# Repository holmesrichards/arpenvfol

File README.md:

# ARP Envelope follower

This is an envelope follower (EF) module in Kosmo format with mic and instrument preamplifiers.

It is a design based on the ARP 2600 — there’s a schematic in the [service manual](https://usermanual.wiki/Document/Arp2600ServiceManual.2176328765). Aside from changing the op amps to TL074 and reducing the output stage gain (which it seemed to need, maybe because it uses ±12 V instead of the ARP's ±15 V) the EF core is essentially identical to the original.

The ARP EF also has a preamplifier section for input of external, non-synth level signals which, of course, are what you’re going to use an EF on a lot of the time. Rather than try to adapt the Teledyne 1339 based design I replaced the ARP preamp with two different preamps: One to boost instrument levels to synth levels, and one to boost mic levels to instrument levels — which then goes through the other preamp as well. This is inspired by Eddie Bergman's [stripboard build](https://www.eddybergman.com/2020/02/synthesizer-build-part-20-arp2600.html), though I used different preamp circuits. The mic preamp is from a [design](http://www.zen22142.zen.co.uk/Circuits/Audio/ecmmic.htm) by Andy Collinson (with a mod from [here](https://electronics.stackexchange.com/questions/324047/%20what-is-the-best-preamplifier-circuit-for-electret-condenser-microphone)) while the instrument preamp is based on the one in Ken Stone’s [Stomp Box Adapter](https://sdiy.info/wiki/CGS_stomp_box_adapter_(smaller_version)). The mic preamp jack supplies power for a two terminal electret condenser mic. For a dynamic mic you may be able to use the instrument input, though I have not tested this.

If nothing’s plugged into the synth input it uses the output of the instrument preamp, and if nothing’s plugged into the input of the instrument preamp it uses the output of the mic preamp. And if nothing’s plugged into the input of the mic preamp it uses the condenser mic capsule mounted on the front panel! Yes, this module is always listening, so be careful what you say. Besides going to the EF input, the instrument preamp output goes to a front panel jack, so you can use this module to feed external signals (or the front panel mic) to other modules too.

This module isn't really a plug and play kind of thing. The output levels you get depend not only on the amplitude of the input signal but the waveform — square waves give bigger outputs than ramp waves, for instance. With an external signal source you will want to use the gain knob to get the preamp output up to around 10 Vpp, and then use the signal level knob to get the output to the right level. It's probably a good idea to use a scope to check your settings.

## Current draw
11.3 mA +12 V, 7.7 mA -12 V

## Photos

## Documentation

* [Schematic](Docs/arpenvfol.pdf)
* PCB layout: [front](Docs/_layout_front.pdf), [back](Docs/_layout_back.pdf)
* [BOM](Docs/arpenvfol_bom.md)
* [Build notes](Docs/build.md)
* [Blog post](https://analogoutputblog.wordpress.com/2022/05/04/arp-2600-based-envelope-follower/)

## GitHub repository

* [https://github.com/holmesrichards/arpenvfol](https://github.com/holmesrichards/arpenvfol)

## Submodules

This repo uses submodules aoKicad and Kosmo_panel, which provide needed libaries for KiCad. To clone:

```
git clone git@github.com:holmesrichards/arpenvfol.git
git submodule init
git submodule update
```

Alternatively do

```
git clone --recurse-submodules git@github.com:holmesrichards/arpenvfol.git
```

Or if you download the repository as a zip file, you must also click on the "aoKicad" and "Kosmo\_panel" links on the GitHub page (they'll have "@ something" after them) and download them as separate zip files which you can unzip into this repo's aoKicad and Kosmo\_panel directories.

If desired, copy the files from aoKicad and Kosmo\_panel to wherever you prefer (your KiCad user library directory, for instance, if you have one). Then in KiCad, go into Edit Symbols and add symbol libraries 

```
aoKicad/ao_symbols
Kosmo_panel/Kosmo
```
and go into Edit Footprints and add footprint libraries 
```
aoKicad/ao_tht
Kosmo_panel/Kosmo_panel.
```

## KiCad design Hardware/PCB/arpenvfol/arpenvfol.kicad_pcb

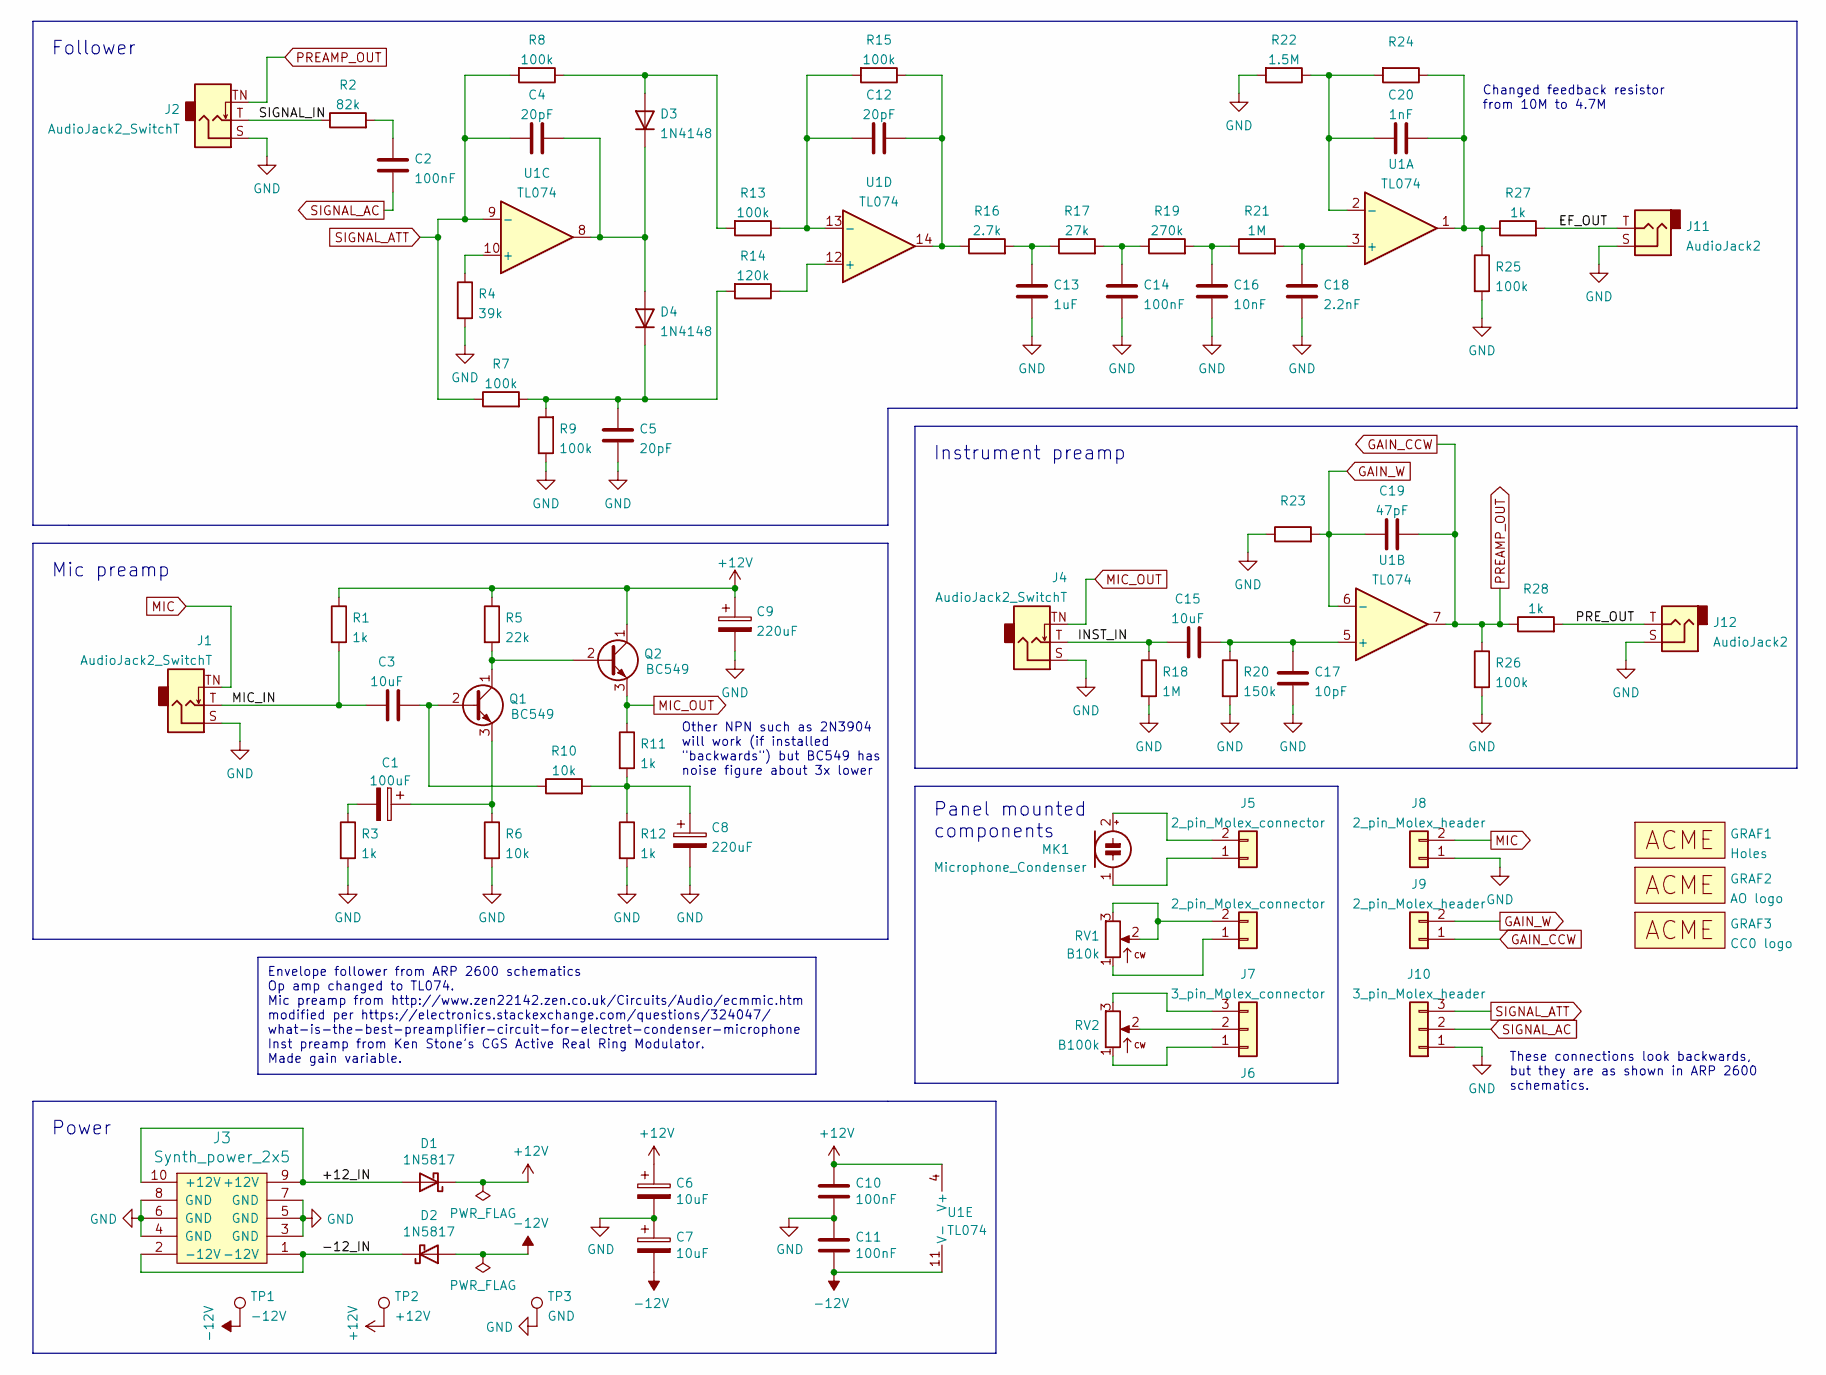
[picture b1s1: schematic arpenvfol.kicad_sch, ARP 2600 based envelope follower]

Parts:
C1: 100uF; CP_Radial_D6.3mm_P2.50mm
C2, C14: 100nF; C_Rect_L7.2mm_W2.5mm_P5.00mm_FKS2_FKP2_MKS2_MKP2
C3, C15: 10uF; C_Radial_D8.0mm_H11.5mm_P3.50mm
C4, C5, C12: 20pF; C_Disc_D5.0mm_W2.5mm_P5.00mm
C6, C7: 10uF; CP_Radial_D6.3mm_P2.50mm
C8, C9: 220uF; CP_Radial_D6.3mm_P2.50mm
C10, C11: 100nF; C_Disc_D3.0mm_W1.6mm_P2.50mm
C13: 1uF; C_Rect_L7.2mm_W7.2mm_P5.00mm_FKS2_FKP2_MKS2_MKP2
C16: 10nF; C_Rect_L7.2mm_W2.5mm_P5.00mm_FKS2_FKP2_MKS2_MKP2
C17: 10pF; C_Disc_D5.0mm_W2.5mm_P5.00mm
C18: 2.2nF; C_Rect_L7.2mm_W2.5mm_P5.00mm_FKS2_FKP2_MKS2_MKP2
C19: 47pF; C_Disc_D5.0mm_W2.5mm_P5.00mm
C20: 1nF; C_Rect_L7.2mm_W2.5mm_P5.00mm_FKS2_FKP2_MKS2_MKP2
D1, D2: 1N5817; D_DO-41_SOD81_P10.16mm_Horizontal
D3, D4: 1N4148; D_DO-35_SOD27_P7.62mm_Horizontal
GRAF1: Holes; arpenvfol_panel_holes
GRAF2: AO logo; analogoutput_12mm
GRAF3: CC0 logo; CC0_logo
J1, J2, J4: AudioJack2_SwitchT; Jack_6.35mm_PJ_629HAN_slots
J3: Synth_power_2x5; Power_Header
J5, J6: 2_pin_Molex_connector; Molex_KK-254_AE-6410-02A_1x02_P2.54mm_Vertical
J7: 3_pin_Molex_connector; Molex_KK-254_AE-6410-03A_1x03_P2.54mm_Vertical
J8, J9: 2_pin_Molex_header; Molex_KK-254_AE-6410-02A_1x02_P2.54mm_Vertical
J10: 3_pin_Molex_header; Molex_KK-254_AE-6410-03A_1x03_P2.54mm_Vertical
J11, J12: AudioJack2; Jack_6.35mm_PJ_629HAN_slots
MK1: Microphone_Condenser
Q1, Q2: BC549; TO-92_Inline_Wide
R1, R3, R11, R12, R27, R28: 1k; R_Axial_DIN0207_L6.3mm_D2.5mm_P10.16mm_Horizontal
R2: 82k; R_Axial_DIN0207_L6.3mm_D2.5mm_P10.16mm_Horizontal
R4: 39k; R_Axial_DIN0207_L6.3mm_D2.5mm_P10.16mm_Horizontal
R5: 22k; R_Axial_DIN0207_L6.3mm_D2.5mm_P10.16mm_Horizontal
R6, R10: 10k; R_Axial_DIN0207_L6.3mm_D2.5mm_P10.16mm_Horizontal
R7, R8, R9, R13, R15, R25, R26: 100k; R_Axial_DIN0207_L6.3mm_D2.5mm_P10.16mm_Horizontal
R14: 120k; R_Axial_DIN0207_L6.3mm_D2.5mm_P10.16mm_Horizontal
R16: 2.7k; R_Axial_DIN0207_L6.3mm_D2.5mm_P10.16mm_Horizontal
R17: 27k; R_Axial_DIN0207_L6.3mm_D2.5mm_P10.16mm_Horizontal
R18, R21: 1M; R_Axial_DIN0207_L6.3mm_D2.5mm_P10.16mm_Horizontal
R19: 270k; R_Axial_DIN0207_L6.3mm_D2.5mm_P10.16mm_Horizontal
R20: 150k; R_Axial_DIN0207_L6.3mm_D2.5mm_P10.16mm_Horizontal
R22: 1.5M; R_Axial_DIN0207_L6.3mm_D2.5mm_P10.16mm_Horizontal
R23, R24: R_Axial_DIN0207_L6.3mm_D2.5mm_P10.16mm_Horizontal
RV1: B10k
RV2: B100k
TP1: -12V; TestPoint_THTPad_D1.5mm_Drill0.7mm
TP2: +12V; TestPoint_THTPad_D1.5mm_Drill0.7mm
TP3: GND; TestPoint_THTPad_1.5x1.5mm_Drill0.7mm
U1: TL074; DIP-14_W7.62mm_Socket_LongPads

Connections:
+12V: C6.1, C9.1, C10.1, D1.1 (K), Q2.1 (C), R1.1, R5.1, TP2.1, U1.4 (V+)
-12V: C7.2, C11.2, D2.2 (A), TP1.1, U1.11 (V-)
/+12_IN: D1.2 (A), J3.9 (+12V), J3.10 (+12V)
/-12_IN: D2.1 (K), J3.1 (-12V), J3.2 (-12V)
/EF_OUT: J11.T, R27.2
/INST_IN: C15.1, J4.T, R18.1
/MIC_IN: C3.1, J1.T, R1.2
/PRE_OUT: J12.T, R28.2
/SIGNAL_IN: J2.T, R2.1
GAIN_CCW: C19.2, J2.TN, J9.1, R26.1, R28.1, U1.7
GAIN_W: C19.1, J9.2, R23.2, U1.6 (-)
GND: C5.2, C6.2, C7.1, C8.2, C9.2, C10.2, C11.1, C13.2, C14.2, C16.2, C17.2, C18.2, J1.S, J2.S, J3.3 (GND), J3.4 (GND), J3.5 (GND), J3.6 (GND), J3.7 (GND), J3.8 (GND), J4.S, J8.1, J10.1, J11.S, J12.S, R3.2, R4.2, R6.2, R9.1, R12.2, R18.2, R20.2, R22.2, R23.1, R25.2, R26.2, TP3.1
MIC: J1.TN, J8.2
MIC_OUT: J4.TN, Q2.3 (E), R11.1
unnamed: C1.1, Q1.3 (E), R6.1
unnamed: C1.2, R3.1
unnamed: C2.1, R2.2
unnamed: C3.2, Q1.2 (B), R10.1
unnamed: C4.2, D3.1 (K), D4.2 (A), U1.8
unnamed: C5.1, D4.1 (K), R7.2, R9.2, R14.2
unnamed: C8.1, R10.2, R11.2, R12.1
unnamed: C12.1, R13.1, R15.2, U1.13 (-)
unnamed: C12.2, R15.1, R16.1, U1.14
unnamed: C13.1, R16.2, R17.1
unnamed: C14.1, R17.2, R19.1
unnamed: C15.2, C17.1, R20.1, U1.5 (+)
unnamed: C16.1, R19.2, R21.1
unnamed: C18.1, R21.2, U1.3 (+)
unnamed: C20.1, R22.1, R24.2, U1.2 (-)
unnamed: C20.2, R24.1, R25.1, R27.1, U1.1
unnamed: D3.2 (A), R8.1, R13.2
unnamed: J5.1, MK1.1 (-)
unnamed: J5.2, MK1.2 (+)
unnamed: J6.1, RV1.1
unnamed: J6.2, RV1.2, RV1.3
unnamed: J7.1, RV2.1
unnamed: J7.2, RV2.2
unnamed: J7.3, RV2.3
unnamed: Q1.1 (C), Q2.2 (B), R5.2
unnamed: R4.1, U1.10 (+)
unnamed: R14.1, U1.12 (+)
SIGNAL_AC: C2.2, J10.2
SIGNAL_ATT: C4.1, J10.3, R7.1, R8.2, U1.9 (-)

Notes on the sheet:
Follower
Other NPN such as 2N3904 will work (if installed "backwards") but BC549 has noise figure about 3x lower
Power
These connections look backwards, but they are as shown in ARP 2600 schematics.
Instrument preamp
Panel mounted components
Changed feedback resistor from 10M to 4.7M
Envelope follower from ARP 2600 schematics Op amp changed to TL074. Mic preamp from http://www.zen22142.zen.co.uk/Circuits/Audio/ecmmic.htm modified per https://electronics.stackexchange.com/questions/324047/ what-is-the-best-preamplifier-circuit-for-electret-condenser-microphone Inst preamp from K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
Mic preamp

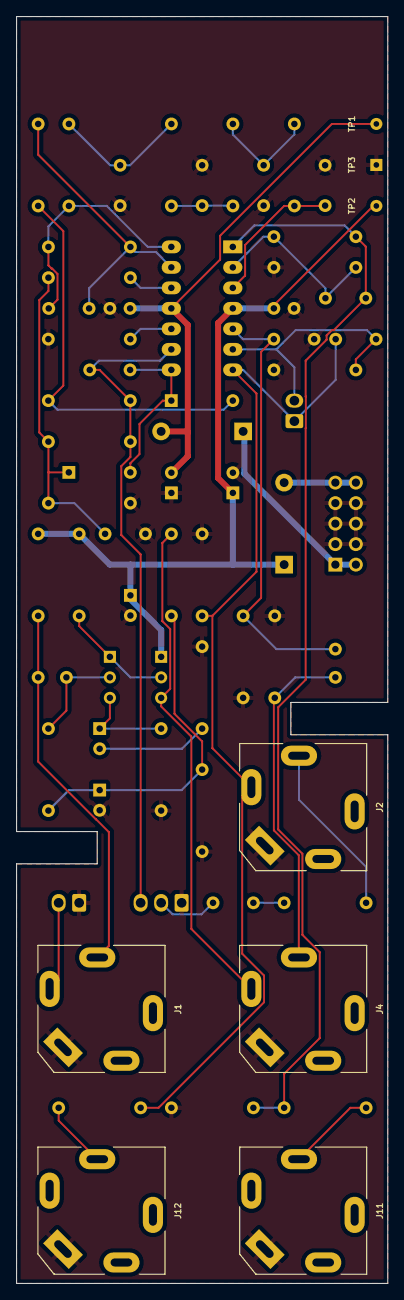
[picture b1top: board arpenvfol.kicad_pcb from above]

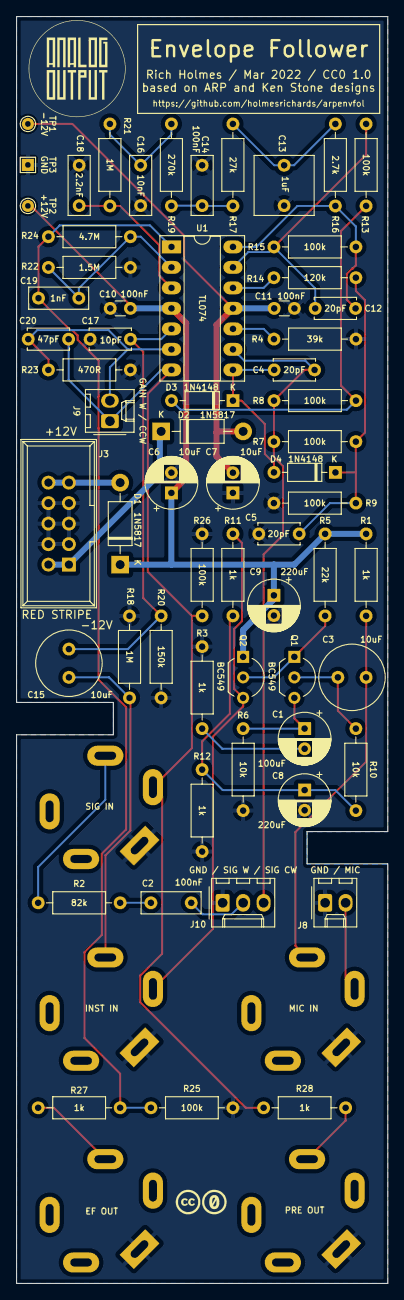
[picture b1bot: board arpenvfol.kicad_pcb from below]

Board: 2 copper layers, 46.0 x 157.0 mm, 70 parts (64 on the bottom side), 36 nets.

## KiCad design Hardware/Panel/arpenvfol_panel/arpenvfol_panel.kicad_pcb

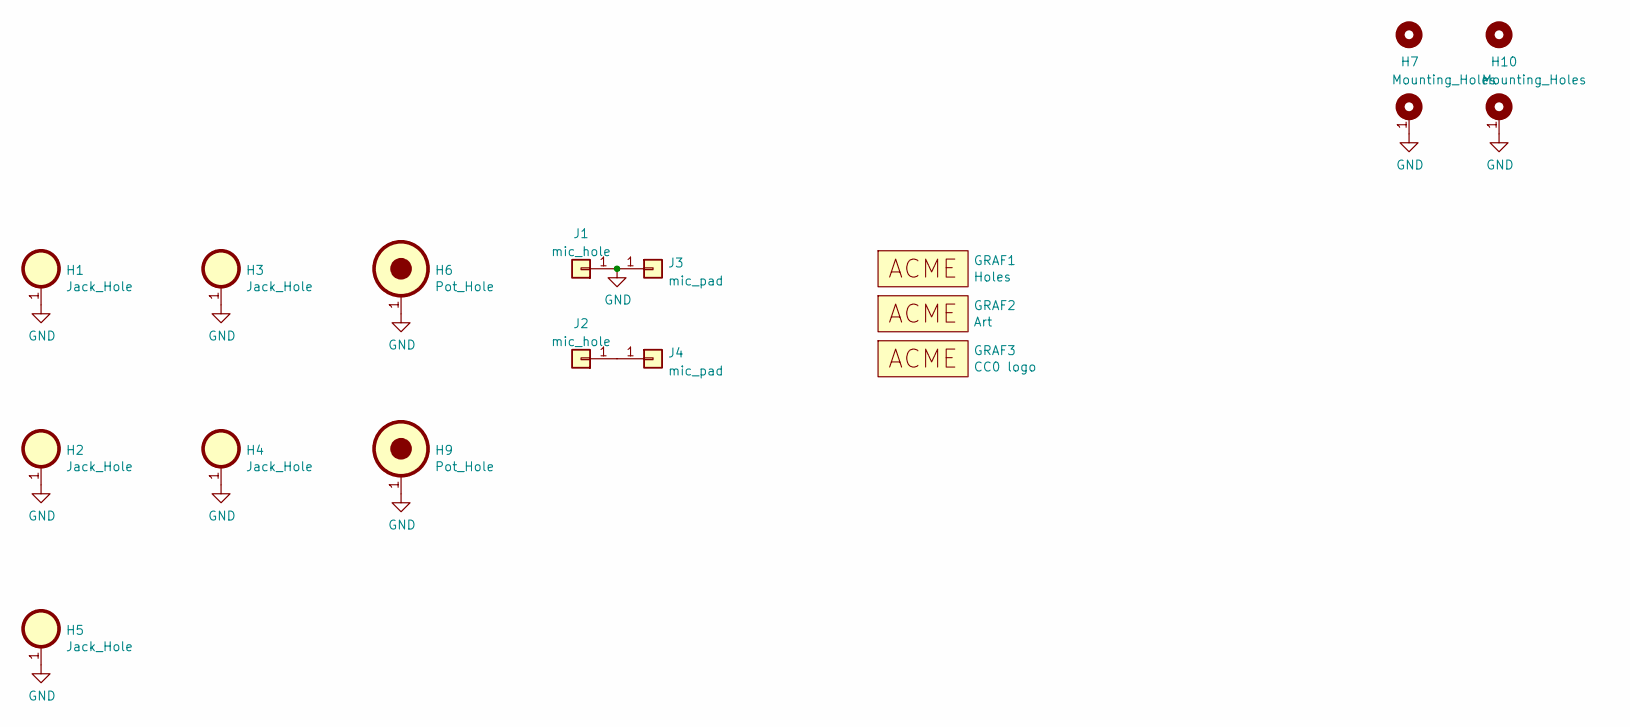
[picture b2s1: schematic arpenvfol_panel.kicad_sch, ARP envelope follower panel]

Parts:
GRAF1: Holes; arpenvfol_panel_holes
GRAF2: Art; arpenvfol_panel_art
GRAF3: CC0 logo; CC0_logo
H1, H2, H3, H4, H5: Jack_Hole; Kosmo_Jack_Hole
H6, H9: Pot_Hole; Kosmo_Pot_Hole
H7, H10: Mounting_Holes; Kosmo_Panel_Dual_Slotted_Mounting_Holes
J1: mic_hole; TestPoint_THTPad_1.5x1.5mm_Drill0.7mm
J2: mic_hole; TestPoint_THTPad_D1.5mm_Drill0.7mm
J3, J4: mic_pad; TestPoint_Pad_D4.0mm

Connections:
GND: H1.1, H2.1, H3.1, H4.1, H5.1, H6.1, H7.1, H9.1, H10.1, J1.1, J3.1
unnamed: J2.1, J4.1

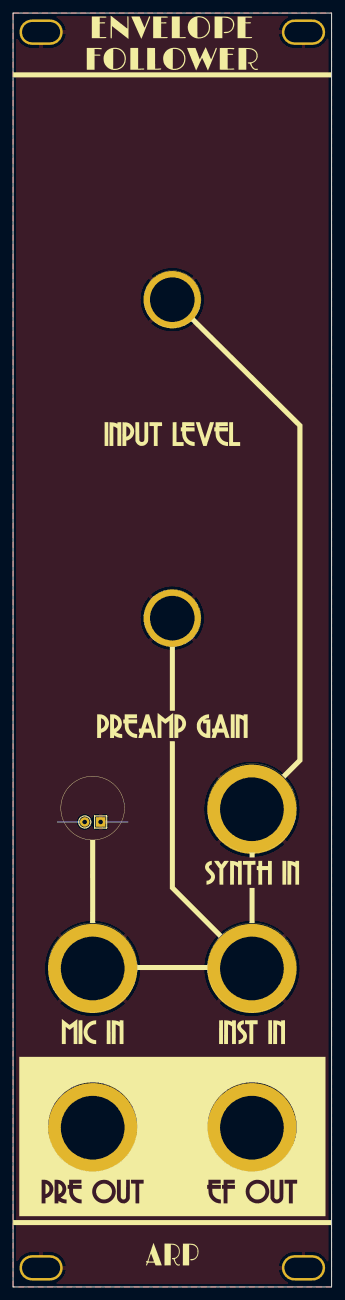
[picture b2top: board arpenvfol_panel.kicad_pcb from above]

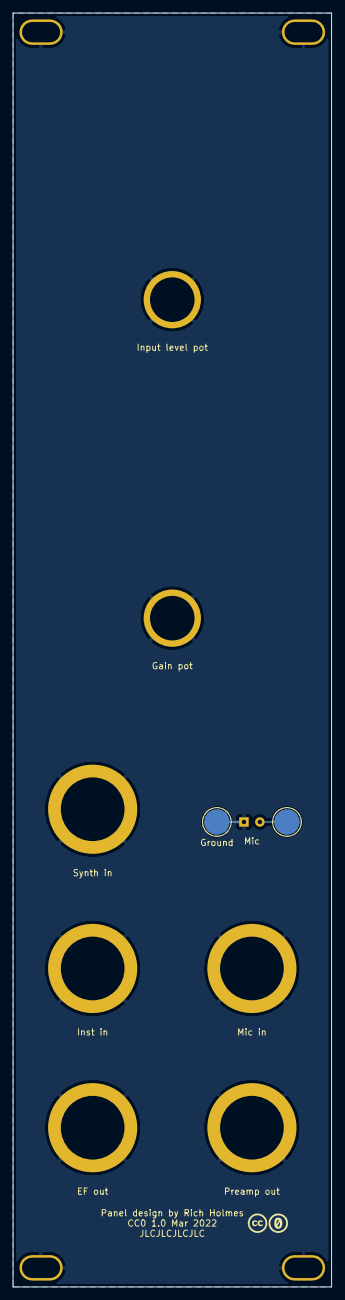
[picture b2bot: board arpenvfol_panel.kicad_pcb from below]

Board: 2 copper layers, 50.0 x 200.0 mm, 16 parts (3 on the bottom side), 2 nets.

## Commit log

2021-11-24 Initial version
2021-11-24 rm cap, add mic
2021-11-25 Update pot symbols
2021-12-05 README edit; design updates; panel art
2021-12-22 NP electrolytics; revise panel
2021-12-25 README
2022-02-01 Better .gitignore; misc revisions
2022-02-14 Reorganize schem; add resistor to mic preamp; change EF gain; add simulation
2022-03-07 Change transistor, annotate, LTSpice simulation
2022-03-26 Panel; add gain pot
2022-04-03 schem tweak
2022-04-11 Schem reorg
2022-05-03 Final pre fab tweaks, Gerbers, schematic, BOM
2022-05-04 Change 2 resistor values
2022-05-04 Revert "Change 2 resistor values"
    This reverts commit a172cd43ee9637b883d7b4f7545da2461ae37f05.
2022-05-04 build docs
2022-05-04 Docs
2022-05-04 Update PCB, layout files
2022-05-04 Create LICENSE
2022-05-05 Libraries updated
2022-05-05 Updated PCB Gerbers
2022-05-09 Blog post
2022-05-10 Note on mic types
2022-05-23 Current draw

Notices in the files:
Hardware/PCB/arpenvfol/arpenvfol.kicad_pcb:
Rich Holmes / Mar 2022 / CC0 1.0
